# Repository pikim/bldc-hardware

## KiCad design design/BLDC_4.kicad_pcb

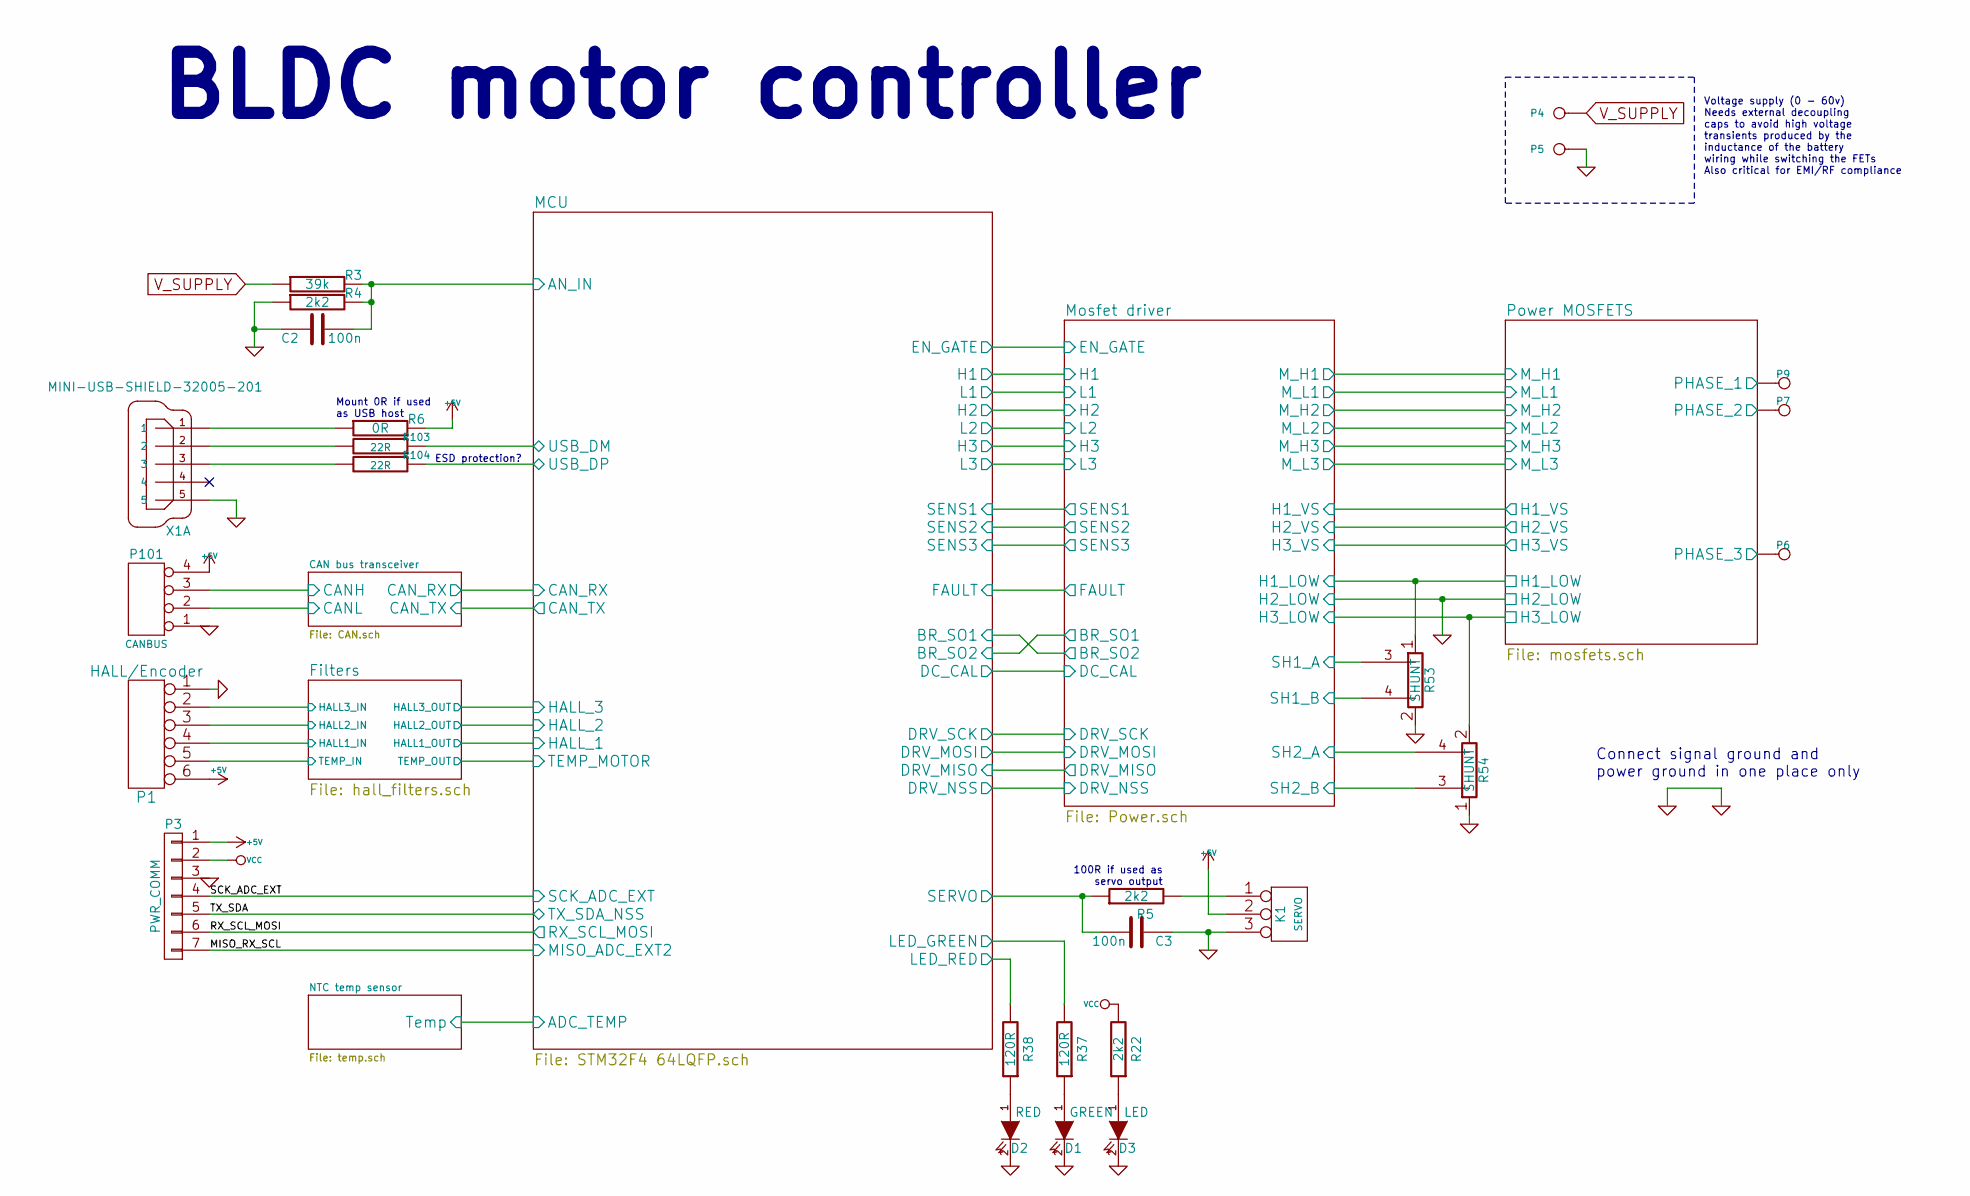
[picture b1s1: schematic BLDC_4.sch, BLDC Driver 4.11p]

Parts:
C2, C3: 100n; SMD-0603_c
D1: GREEN; LED-0603
D2: RED; LED-0603
D3: LED; LED-0603
K1: SERVO; pinhead-1X03
P1: HALL/Encoder; b6b-ph-kl
P3: PWR_COMM; b7b-ph-kl
P4: IN+; 1PAD_4x5mm
P5: IN-; 1PAD_4x5mm
P6: MOTOR1; 1PAD_4x5mm
P7: MOTOR2; 1PAD_4x5mm
P9: MOTOR3; 1PAD_4x5mm
P101: CANBUS; b4b-ph-kl
R3: 39k; SMD-0603_r
R4, R5, R22: 2k2; SMD-0603_r
R6: 0R; SMD-0603_r
R37, R38: 120R; SMD-0603_r
R53, R54: SHUNT; WSLP2726
R103, R104: 22R; SMD-0603_r
X1: MINI-USB-SHIELD-32005-201; USB-UX60R-MB-5ST

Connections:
+5V: K1.2 (PM), P1.6, P3.1, P101.4, R6.2; also elsewhere on the board
/CAN bus transceiver/CANH: P101.3; also elsewhere on the board
/CAN bus transceiver/CANL: P101.2; also elsewhere on the board
/Filters/HALL1_IN: P1.4; also elsewhere on the board
/Filters/HALL2_IN: P1.3; also elsewhere on the board
/Filters/HALL3_IN: P1.2; also elsewhere on the board
/Filters/TEMP_IN: P1.5; also elsewhere on the board
/MCU/AN_IN: C2.2, R3.2, R4.2; also elsewhere on the board
/MCU/LED_GREEN: R37.2; also elsewhere on the board
/MCU/LED_RED: R38.2; also elsewhere on the board
/MCU/MISO_ADC_EXT2: P3.7; also elsewhere on the board
/MCU/RX_SCL_MOSI: P3.6; also elsewhere on the board
/MCU/SCK_ADC_EXT: P3.4; also elsewhere on the board
/MCU/SERVO: C3.2, R5.1; also elsewhere on the board
/MCU/TX_SDA_NSS: P3.5; also elsewhere on the board
/MCU/USB_DM: R103.1; also elsewhere on the board
/MCU/USB_DP: R104.1; also elsewhere on the board
/Mosfet driver/H1_LOW: R53.1; also elsewhere on the board
/Mosfet driver/H1_VS: P9.1; also elsewhere on the board
/Mosfet driver/H2_VS: P7.1; also elsewhere on the board
/Mosfet driver/H3_LOW: R54.2; also elsewhere on the board
/Mosfet driver/H3_VS: P6.1; also elsewhere on the board
/Mosfet driver/SH1_A: R53.3; also elsewhere on the board
/Mosfet driver/SH1_B: R53.4; also elsewhere on the board
/Mosfet driver/SH2_A: R54.4; also elsewhere on the board
/Mosfet driver/SH2_B: R54.3; also elsewhere on the board
GND: C2.1, C3.1, D1.2 (K), D2.2 (K), D3.2 (K), K1.3, P1.1, P3.3, P5.1, P101.1, R4.1, R53.2, R54.1, X1.5; also elsewhere on the board
unnamed: D1.1 (A), R37.1
unnamed: D2.1 (A), R38.1
unnamed: D3.1 (A), R22.1
unnamed: K1.1, R5.2
unnamed: R6.1, X1.1
unnamed: R103.2, X1.2
unnamed: R104.2, X1.3
VCC: P3.2, R22.2; also elsewhere on the board
V_SUPPLY: P4.1, R3.1; also elsewhere on the board

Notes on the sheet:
100R if used as servo output
Mount 0R if used as USB host
ESD protection?
BLDC motor controller
Voltage supply (0 - 60v) Needs external decoupling caps to avoid high voltage transients produced by the inductance of the battery wiring while switching the FETs Also critical for EMI/RF compliance
Connect signal ground and power ground in one place only

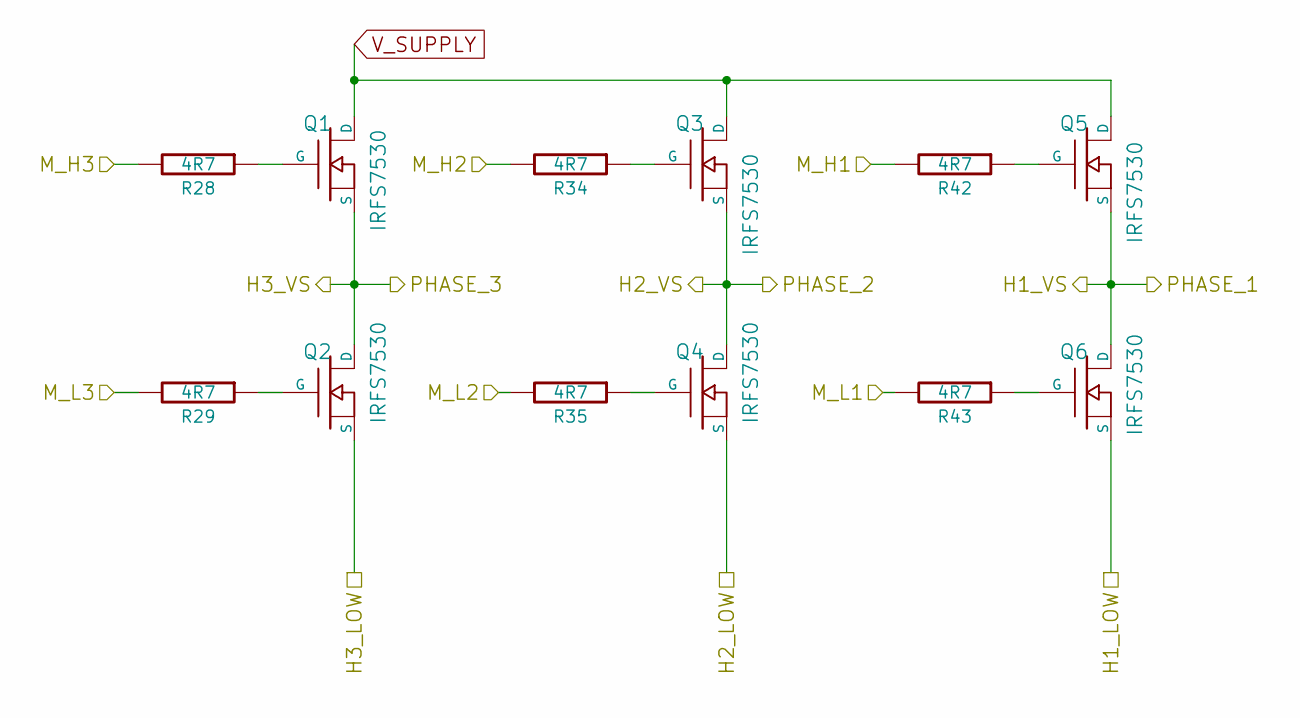
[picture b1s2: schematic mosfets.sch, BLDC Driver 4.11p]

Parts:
Q1, Q2, Q3, Q4, Q5, Q6: IRFS7530; D2PAK-7-GDS
R28, R29, R34, R35, R42, R43: 4R7; SMD-0603_r

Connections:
/Mosfet driver/H1_LOW: Q6.S; also elsewhere on the board
/Mosfet driver/H1_VS: Q5.S, Q6.D; also elsewhere on the board
/Mosfet driver/H2_VS: Q3.S, Q4.D; also elsewhere on the board
/Mosfet driver/H3_LOW: Q2.S; also elsewhere on the board
/Mosfet driver/H3_VS: Q1.S, Q2.D; also elsewhere on the board
/Mosfet driver/M_H1: R42.2; also elsewhere on the board
/Mosfet driver/M_H2: R34.2; also elsewhere on the board
/Mosfet driver/M_H3: R28.2; also elsewhere on the board
/Mosfet driver/M_L1: R43.2; also elsewhere on the board
/Mosfet driver/M_L2: R35.2; also elsewhere on the board
/Mosfet driver/M_L3: R29.2; also elsewhere on the board
GND: Q4.S; also elsewhere on the board
unnamed: Q1.G, R28.1
unnamed: Q2.G, R29.1
unnamed: Q3.G, R34.1
unnamed: Q4.G, R35.1
unnamed: Q5.G, R42.1
unnamed: Q6.G, R43.1
V_SUPPLY: Q1.D, Q3.D, Q5.D; also elsewhere on the board

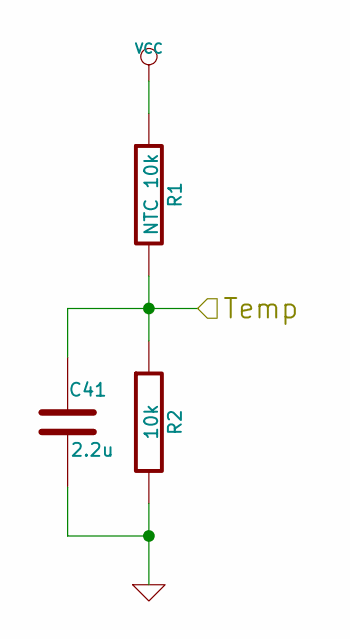
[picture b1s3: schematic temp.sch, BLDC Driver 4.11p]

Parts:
C41: 2.2u; SMD-0603_c; Part# GRM188R61C225KAAD or GRM188C81A225KAAD
R1: NTC 10k; SMD-0603_r
R2: 10k; SMD-0603_r

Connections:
/MCU/ADC_TEMP: C41.1, R1.2, R2.1; also elsewhere on the board
GND: C41.2, R2.2; also elsewhere on the board
VCC: R1.1; also elsewhere on the board

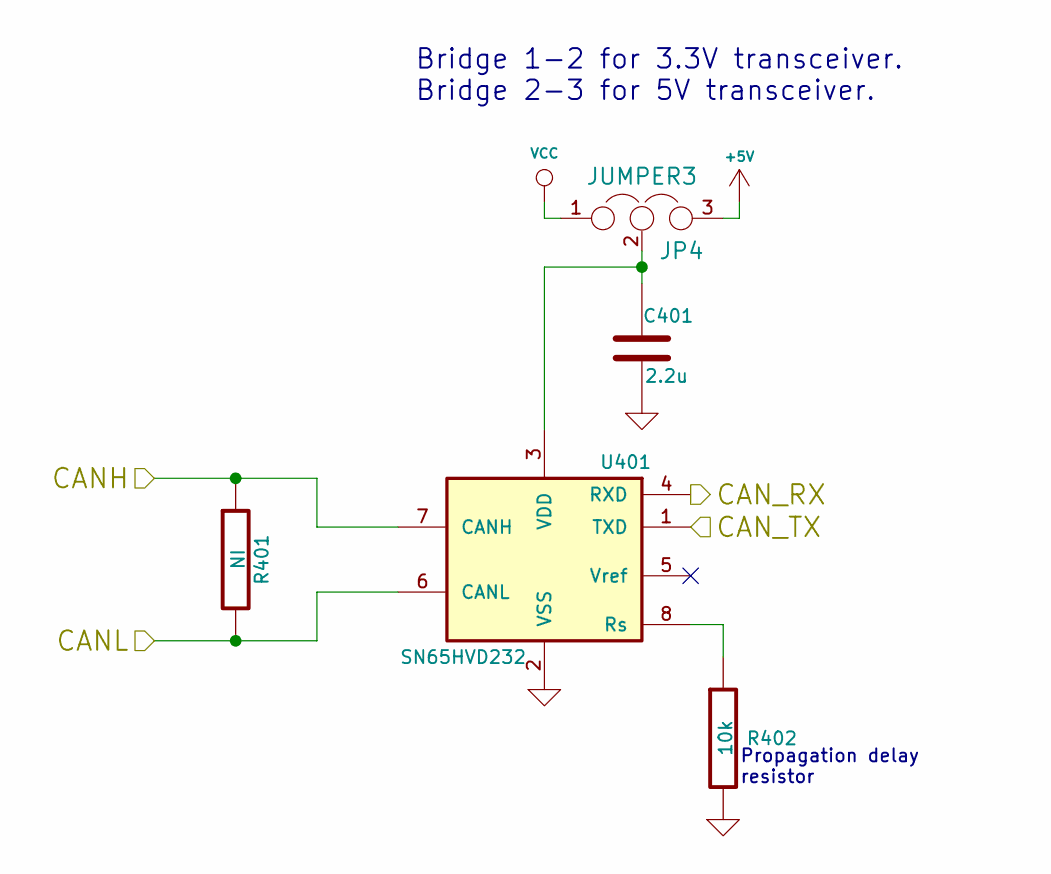
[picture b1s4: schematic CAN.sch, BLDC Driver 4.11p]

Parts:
C401: 2.2u; SMD-0603_c; Part# GRM188R61C225KAAD or GRM188C81A225KAAD
JP4: JUMPER3; S_JUMPER_3
R401: NI; SMD-0603_r
R402: 10k; SMD-0603_r
U401: SN65HVD232; SOIC-8-W

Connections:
+5V: JP4.3; also elsewhere on the board
/CAN bus transceiver/CANH: R401.1, U401.7 (CANH); also elsewhere on the board
/CAN bus transceiver/CANL: R401.2, U401.6 (CANL); also elsewhere on the board
/CAN bus transceiver/CAN_RX: U401.4 (RXD); also elsewhere on the board
/CAN bus transceiver/CAN_TX: U401.1 (TXD); also elsewhere on the board
GND: C401.2, R402.2, U401.2 (VSS); also elsewhere on the board
unnamed: C401.1, JP4.2, U401.3 (VDD)
unnamed: R402.1, U401.8 (Rs)
VCC: JP4.1; also elsewhere on the board

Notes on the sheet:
Propagation delay resistor
Bridge 1-2 for 3.3V transceiver. Bridge 2-3 for 5V transceiver.

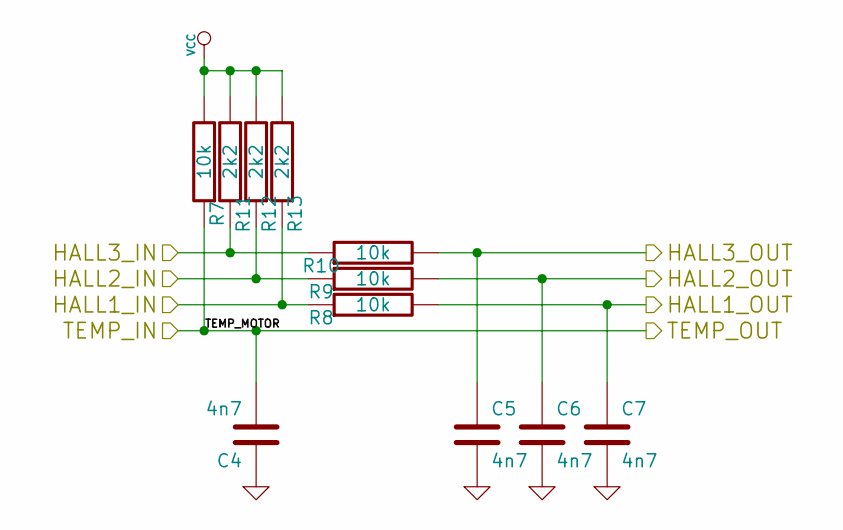
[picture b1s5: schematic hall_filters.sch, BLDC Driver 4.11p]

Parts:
C4, C5, C6, C7: 4n7; SMD-0603_c
R7, R8, R9, R10: 10k; SMD-0603_r
R11, R12, R13: 2k2; SMD-0603_r

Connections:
/Filters/HALL1_IN: R8.1, R13.1; also elsewhere on the board
/Filters/HALL1_OUT: C7.1, R8.2; also elsewhere on the board
/Filters/HALL2_IN: R9.1, R12.1; also elsewhere on the board
/Filters/HALL2_OUT: C6.1, R9.2; also elsewhere on the board
/Filters/HALL3_IN: R10.1, R11.1; also elsewhere on the board
/Filters/HALL3_OUT: C5.1, R10.2; also elsewhere on the board
/Filters/TEMP_IN: C4.2, R7.1; also elsewhere on the board
GND: C4.1, C5.2, C6.2, C7.2; also elsewhere on the board
VCC: R7.2, R11.2, R12.2, R13.2; also elsewhere on the board

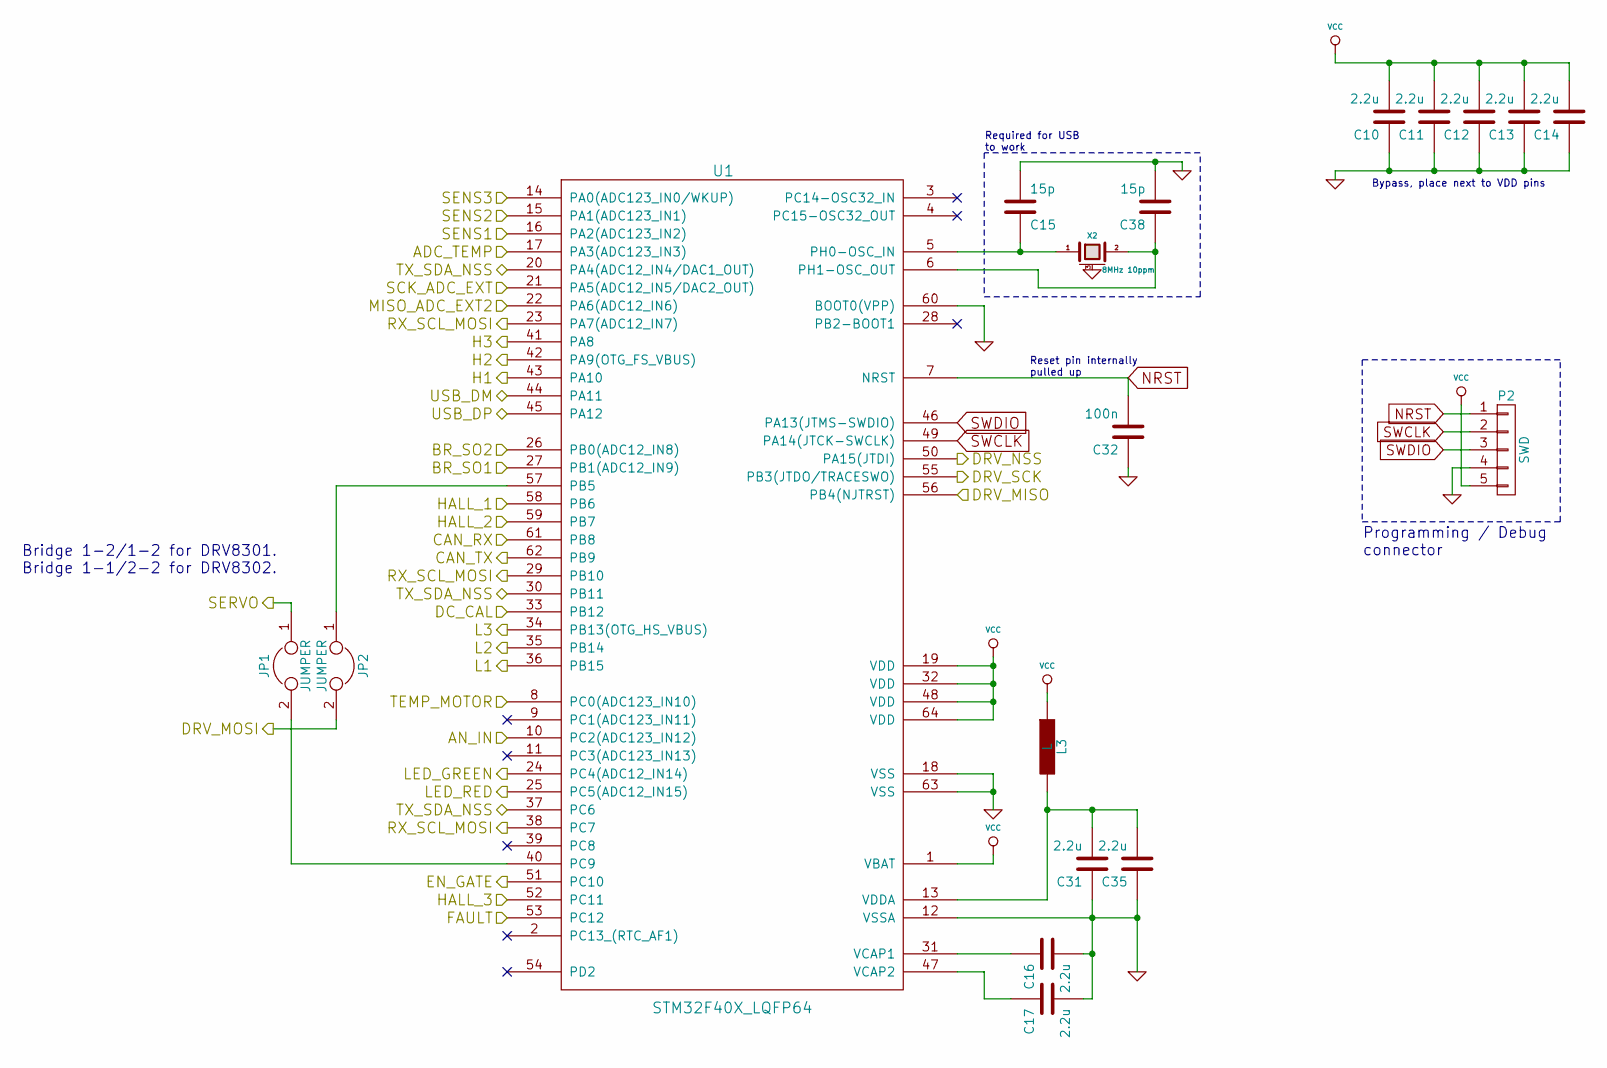
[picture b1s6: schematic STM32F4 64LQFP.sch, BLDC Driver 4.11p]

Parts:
C10, C11, C12, C13, C14, C16, C17, C31, C35: 2.2u; SMD-0603_c; Part# GRM188R61C225KAAD or GRM188C81A225KAAD
C15, C38: 15p; SMD-0603_c
C32: 100n; SMD-0603_c
JP1, JP2: JUMPER; S_JUMPER_2
L3: L; SMD-0603_r
P2: SWD; Pin_Header_Straight_1x05
U1: STM32F40X_LQFP64; lqfp64_pad_mod
X2: 8MHz 10ppm; Crystal_5x3mm; Part# ABM3B-8.0-10-1UT

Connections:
/CAN bus transceiver/CAN_RX: U1.61 (PB8); also elsewhere on the board
/CAN bus transceiver/CAN_TX: U1.62 (PB9); also elsewhere on the board
/Filters/HALL1_OUT: U1.58 (PB6); also elsewhere on the board
/Filters/HALL2_OUT: U1.59 (PB7); also elsewhere on the board
/Filters/HALL3_OUT: U1.52 (PC11); also elsewhere on the board
/Filters/TEMP_IN: U1.8 (PC0(ADC123_IN10)); also elsewhere on the board
/MCU/ADC_TEMP: U1.17 (PA3(ADC123_IN3)); also elsewhere on the board
/MCU/AN_IN: U1.10 (PC2(ADC123_IN12)); also elsewhere on the board
/MCU/BR_SO1: U1.27 (PB1(ADC12_IN9)); also elsewhere on the board
/MCU/DC_CAL: U1.33 (PB12); also elsewhere on the board
/MCU/DRV_MISO: U1.56 (PB4(NJTRST)); also elsewhere on the board
/MCU/DRV_MOSI: JP2.2; also elsewhere on the board
/MCU/DRV_NSS: U1.50 (PA15(JTDI)); also elsewhere on the board
/MCU/DRV_SCK: U1.55 (PB3(JTDO/TRACESWO)); also elsewhere on the board
/MCU/EN_GATE: U1.51 (PC10); also elsewhere on the board
/MCU/FAULT: U1.53 (PC12); also elsewhere on the board
/MCU/H1: U1.43 (PA10); also elsewhere on the board
/MCU/H2: U1.42 (PA9(OTG_FS_VBUS)); also elsewhere on the board
/MCU/H3: U1.41 (PA8); also elsewhere on the board
/MCU/L1: U1.36 (PB15); also elsewhere on the board
/MCU/L2: U1.35 (PB14); also elsewhere on the board
/MCU/L3: U1.34 (PB13(OTG_HS_VBUS)); also elsewhere on the board
/MCU/LED_GREEN: U1.24 (PC4(ADC12_IN14)); also elsewhere on the board
/MCU/LED_RED: U1.25 (PC5(ADC12_IN15)); also elsewhere on the board
/MCU/MISO_ADC_EXT2: U1.22 (PA6(ADC12_IN6)); also elsewhere on the board
/MCU/RX_SCL_MOSI: U1.23 (PA7(ADC12_IN7)), U1.29 (PB10), U1.38 (PC7); also elsewhere on the board
/MCU/SCK_ADC_EXT: U1.21 (PA5(ADC12_IN5/DAC2_OUT)); also elsewhere on the board
/MCU/SENS1: U1.16 (PA2(ADC123_IN2)); also elsewhere on the board
/MCU/SENS2: U1.15 (PA1(ADC123_IN1)); also elsewhere on the board
/MCU/SENS3: U1.14 (PA0(ADC123_IN0/WKUP)); also elsewhere on the board
/MCU/SERVO: JP1.1; also elsewhere on the board
/MCU/TX_SDA_NSS: U1.20 (PA4(ADC12_IN4/DAC1_OUT)), U1.30 (PB11), U1.37 (PC6); also elsewhere on the board
/MCU/USB_DM: U1.44 (PA11); also elsewhere on the board
/MCU/USB_DP: U1.45 (PA12); also elsewhere on the board
/Mosfet driver/BR_SO1: U1.26 (PB0(ADC12_IN8)); also elsewhere on the board
GND: C10.1, C11.1, C12.1, C13.1, C14.1, C15.2, C16.2, C17.2, C31.1, C32.1, C35.1, C38.2, P2.4, U1.12 (VSSA), U1.18 (VSS), U1.60 (BOOT0(VPP)), U1.63 (VSS), X2.3 (case); also elsewhere on the board
NRST: C32.2, P2.1, U1.7 (NRST)
unnamed: C15.1, U1.5 (PH0-OSC_IN), X2.1
unnamed: C16.1, U1.31 (VCAP1)
unnamed: C17.1, U1.47 (VCAP2)
unnamed: C31.2, C35.2, L3.2, U1.13 (VDDA)
unnamed: C38.1, U1.6 (PH1-OSC_OUT), X2.2
unnamed: JP1.2, U1.40 (PC9)
unnamed: JP2.1, U1.57 (PB5)
SWCLK: P2.2, U1.49 (PA14(JTCK-SWCLK))
SWDIO: P2.3, U1.46 (PA13(JTMS-SWDIO))
VCC: C10.2, C11.2, C12.2, C13.2, C14.2, L3.1, P2.5, U1.1 (VBAT), U1.19 (VDD), U1.32 (VDD), U1.48 (VDD), U1.64 (VDD); also elsewhere on the board

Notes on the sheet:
Programming / Debug connector
Reset pin internally pulled up
Required for USB to work
Bypass, place next to VDD pins
Bridge 1-2/1-2 for DRV8301. Bridge 1-1/2-2 for DRV8302.

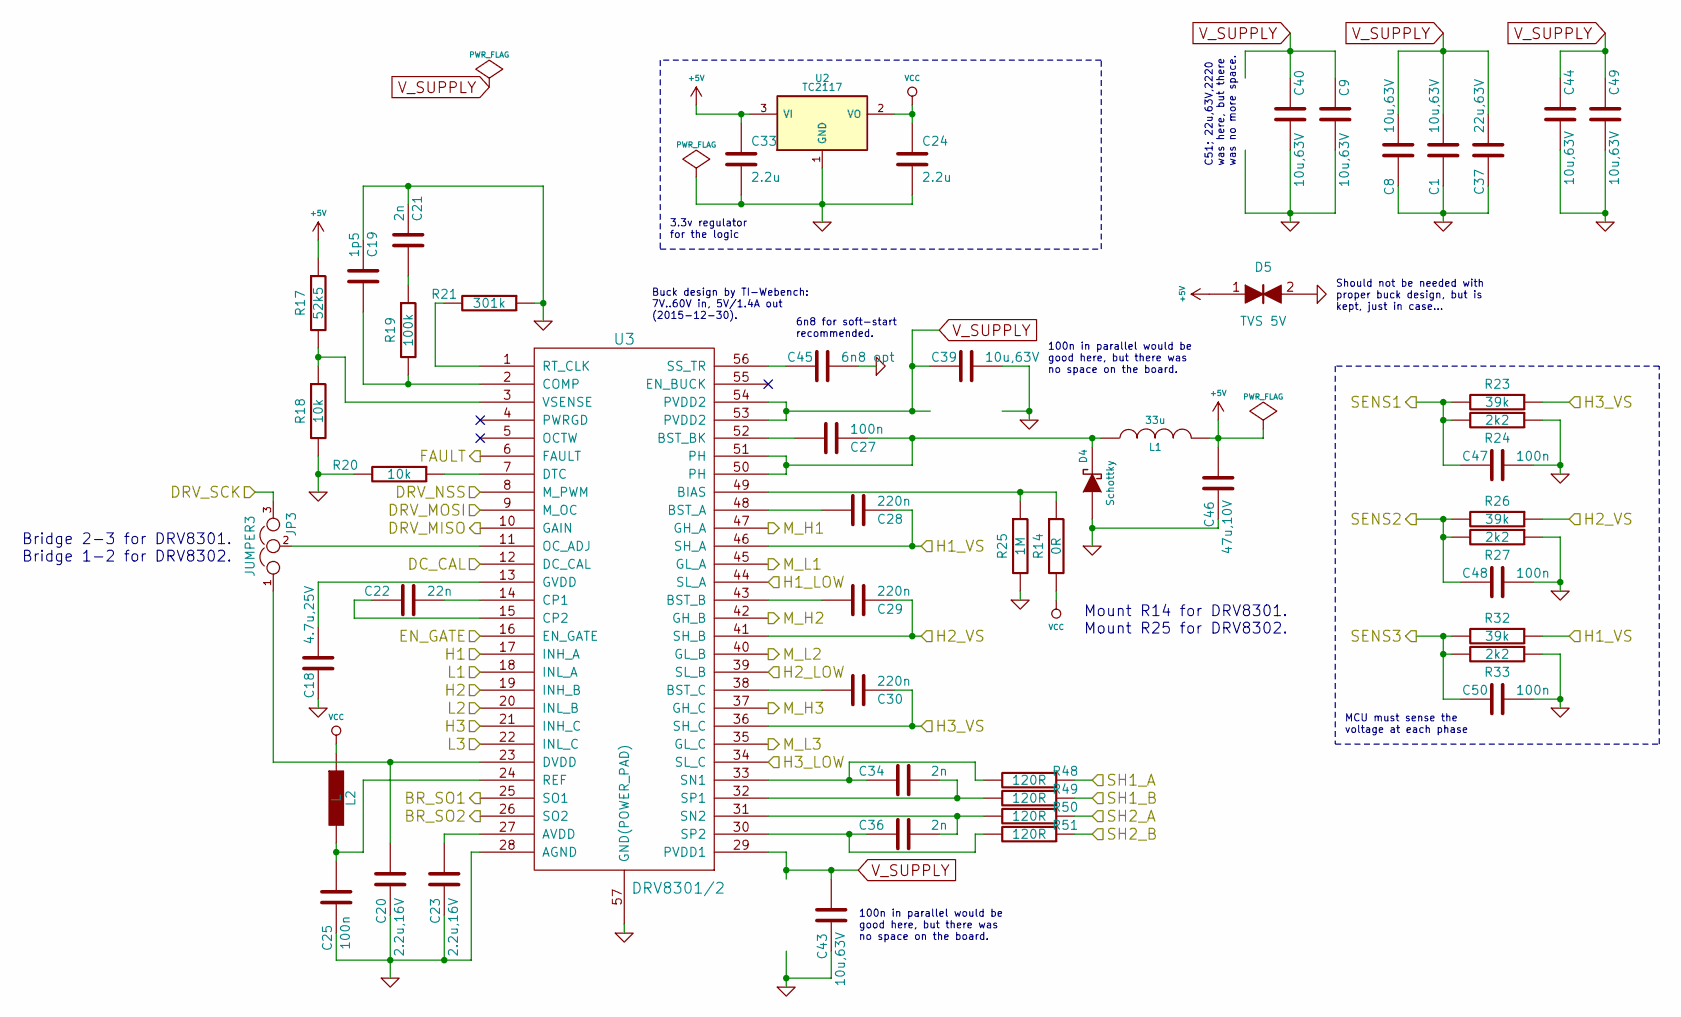
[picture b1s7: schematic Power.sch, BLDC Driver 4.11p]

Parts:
C1, C8, C9, C39, C40, C43, C44, C49: 10u,63V; c_1210; Part# GRM32ER71J106KA12
C18: 4.7u,25V; SMD-0603_c; Part# GRM188R61E475KE15
C19: 1p5; SMD-0603_c
C20, C23: 2.2u,16V; SMD-0603_c; Part# GRM188R61C225KAAD
C21, C34, C36: 2n; SMD-0603_c
C22: 22n; SMD-0603_c
C24, C33: 2.2u; SMD-0603_c; Part# GRM188R61C225KAAD or GRM188C81A225KAAD
C25, C27, C47, C48, C50: 100n; SMD-0603_c
C28, C29, C30: 220n; SMD-0603_c
C37: 22u,63V; c_2220; Part# KRM55WR71J226MH01
C45: 6n8 opt; SMD-0603_c
C46: 47u,10V; c_1210; Part# GRM32ER61A476KE20
D4: Schottky; SMA_Standard
D5: TVS 5V; SMA_Standard
JP3: JUMPER3; S_JUMPER_3
L1: 33u; inductor_smd_6x6mm
L2: L; SMD-0603_r
R14: 0R; SMD-0603_r
R17: 52k5; SMD-0603_r
R18, R20: 10k; SMD-0603_r
R19: 100k; SMD-0603_r
R21: 301k; SMD-0603_r
R23, R26, R32: 39k; SMD-0603_r
R24, R27, R33: 2k2; SMD-0603_r
R25: 1M; SMD-0603_r
R48, R49, R50, R51: 120R; SMD-0603_r
U2: TC2117; SOT-223
U3: DRV8301/2; TSSOP-56-PP

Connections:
+5V: C33.1, C46.1, D5.1, L1.2, R17.1, U2.3 (VI); also elsewhere on the board
/MCU/BR_SO1: U3.26 (SO2); also elsewhere on the board
/MCU/DC_CAL: U3.12 (DC_CAL); also elsewhere on the board
/MCU/DRV_MISO: U3.10 (GAIN); also elsewhere on the board
/MCU/DRV_MOSI: U3.9 (M_OC); also elsewhere on the board
/MCU/DRV_NSS: U3.8 (M_PWM); also elsewhere on the board
/MCU/DRV_SCK: JP3.3; also elsewhere on the board
/MCU/EN_GATE: U3.16 (EN_GATE); also elsewhere on the board
/MCU/FAULT: U3.6 (FAULT); also elsewhere on the board
/MCU/H1: U3.17 (INH_A); also elsewhere on the board
/MCU/H2: U3.19 (INH_B); also elsewhere on the board
/MCU/H3: U3.21 (INH_C); also elsewhere on the board
/MCU/L1: U3.18 (INL_A); also elsewhere on the board
/MCU/L2: U3.20 (INL_B); also elsewhere on the board
/MCU/L3: U3.22 (INL_C); also elsewhere on the board
/MCU/SENS1: C47.2, R23.2, R24.2; also elsewhere on the board
/MCU/SENS2: C48.2, R26.2, R27.2; also elsewhere on the board
/MCU/SENS3: C50.2, R32.2, R33.2; also elsewhere on the board
/Mosfet driver/BR_SO1: U3.25 (SO1); also elsewhere on the board
/Mosfet driver/H1_LOW: U3.44 (SL_A); also elsewhere on the board
/Mosfet driver/H1_VS: C28.1, R32.1, U3.46 (SH_A); also elsewhere on the board
/Mosfet driver/H2_VS: C29.1, R26.1, U3.41 (SH_B); also elsewhere on the board
/Mosfet driver/H3_LOW: U3.34 (SL_C); also elsewhere on the board
/Mosfet driver/H3_VS: C30.1, R23.1, U3.36 (SH_C); also elsewhere on the board
/Mosfet driver/M_H1: U3.47 (GH_A); also elsewhere on the board
/Mosfet driver/M_H2: U3.42 (GH_B); also elsewhere on the board
/Mosfet driver/M_H3: U3.37 (GH_C); also elsewhere on the board
/Mosfet driver/M_L1: U3.45 (GL_A); also elsewhere on the board
/Mosfet driver/M_L2: U3.40 (GL_B); also elsewhere on the board
/Mosfet driver/M_L3: U3.35 (GL_C); also elsewhere on the board
/Mosfet driver/SH1_A: R48.1; also elsewhere on the board
/Mosfet driver/SH1_B: R49.1; also elsewhere on the board
/Mosfet driver/SH2_A: R50.1; also elsewhere on the board
/Mosfet driver/SH2_B: R51.1; also elsewhere on the board
GND: C1.1, C8.1, C9.1, C18.2, C19.1, C20.1, C21.1, C23.1, C24.2, C25.1, C33.2, C37.1, C39.1, C40.1, C43.2, C44.2, C45.1, C46.2, C47.1, C48.1, C49.2, C50.1, D4.1 (A), D5.2, R18.2, R20.2, R21.1, R24.1, R25.2, R27.1, R33.1, U2.1 (GND), U3.28 (AGND), U3.39 (SL_B), U3.57 (GND(POWER_PAD)); also elsewhere on the board
unnamed: C18.1, U3.13 (GVDD)
unnamed: C19.2, R19.2, U3.2 (COMP)
unnamed: C20.2, JP3.1, U3.23 (DVDD)
unnamed: C21.2, R19.1
unnamed: C22.1, U3.14 (CP1)
unnamed: C22.2, U3.15 (CP2)
unnamed: C23.2, U3.27 (AVDD)
unnamed: C25.2, L2.2, U3.24 (REF)
unnamed: C27.1, D4.2 (K), L1.1, U3.50 (PH), U3.51 (PH)
unnamed: C27.2, U3.52 (BST_BK)
unnamed: C28.2, U3.48 (BST_A)
unnamed: C29.2, U3.43 (BST_B)
unnamed: C30.2, U3.38 (BST_C)
unnamed: C34.1, R48.2, U3.33 (SN1)
unnamed: C34.2, R49.2, U3.32 (SP1)
unnamed: C36.1, R51.2, U3.30 (SP2)
unnamed: C36.2, R50.2, U3.31 (SN2)
unnamed: C45.2, U3.56 (SS_TR)
unnamed: JP3.2, U3.11 (OC_ADJ)
unnamed: R14.1, R25.1, U3.49 (BIAS)
unnamed: R17.2, R18.1, U3.3 (VSENSE)
unnamed: R20.1, U3.7 (DTC)
unnamed: R21.2, U3.1 (RT_CLK)
VCC: C24.1, L2.1, R14.2, U2.2 (VO); also elsewhere on the board
V_SUPPLY: C1.2, C8.2, C9.2, C37.2, C39.2, C40.2, C43.1, C44.1, C49.1, U3.29 (PVDD1), U3.53 (PVDD2), U3.54 (PVDD2); also elsewhere on the board

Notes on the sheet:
MCU must sense the voltage at each phase
3.3v regulator for the logic
Buck design by TI-Webench: 7V..60V in, 5V/1.4A out (2015-12-30).
C51; 22u,63V,2220 was here, but there was no more space.
100n in parallel would be good here, but there was no space on the board.
6n8 for soft-start recommended.
Should not be needed with proper buck design, but is kept, just in case...
Bridge 2-3 for DRV8301. Bridge 1-2 for DRV8302.
Mount R14 for DRV8301. Mount R25 for DRV8302.

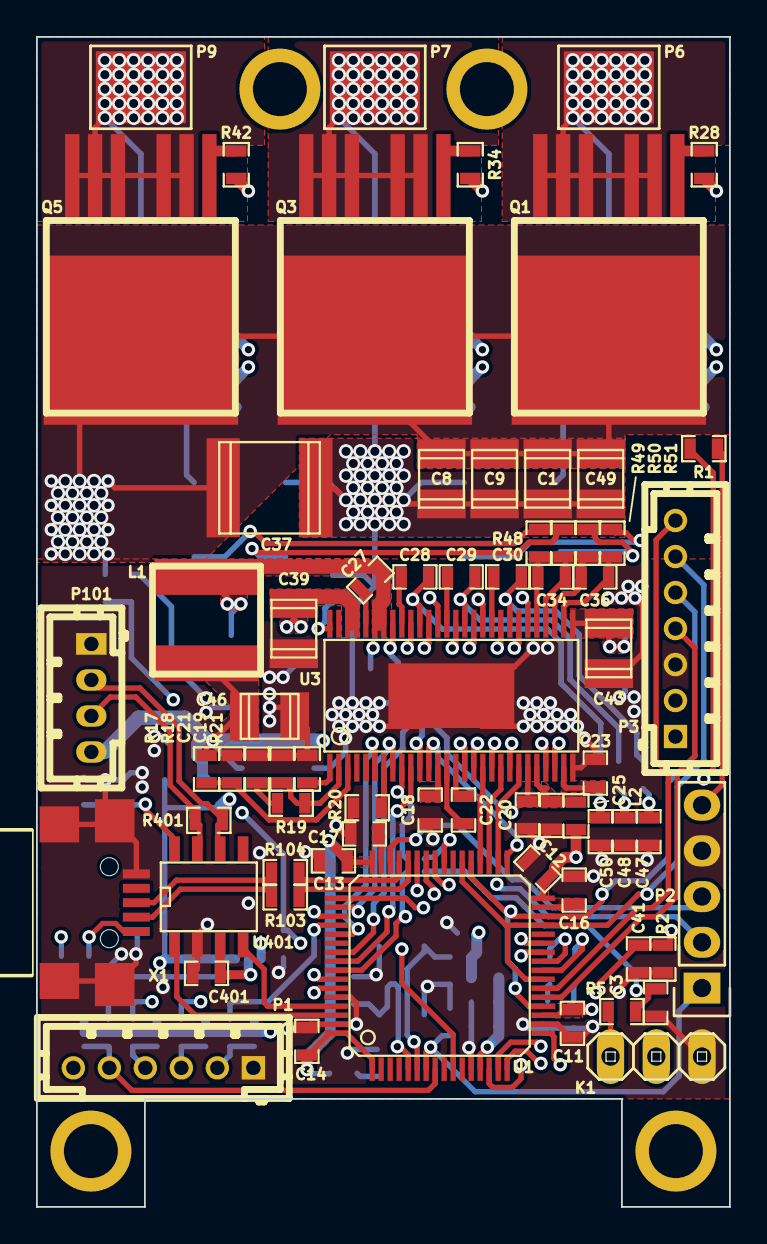
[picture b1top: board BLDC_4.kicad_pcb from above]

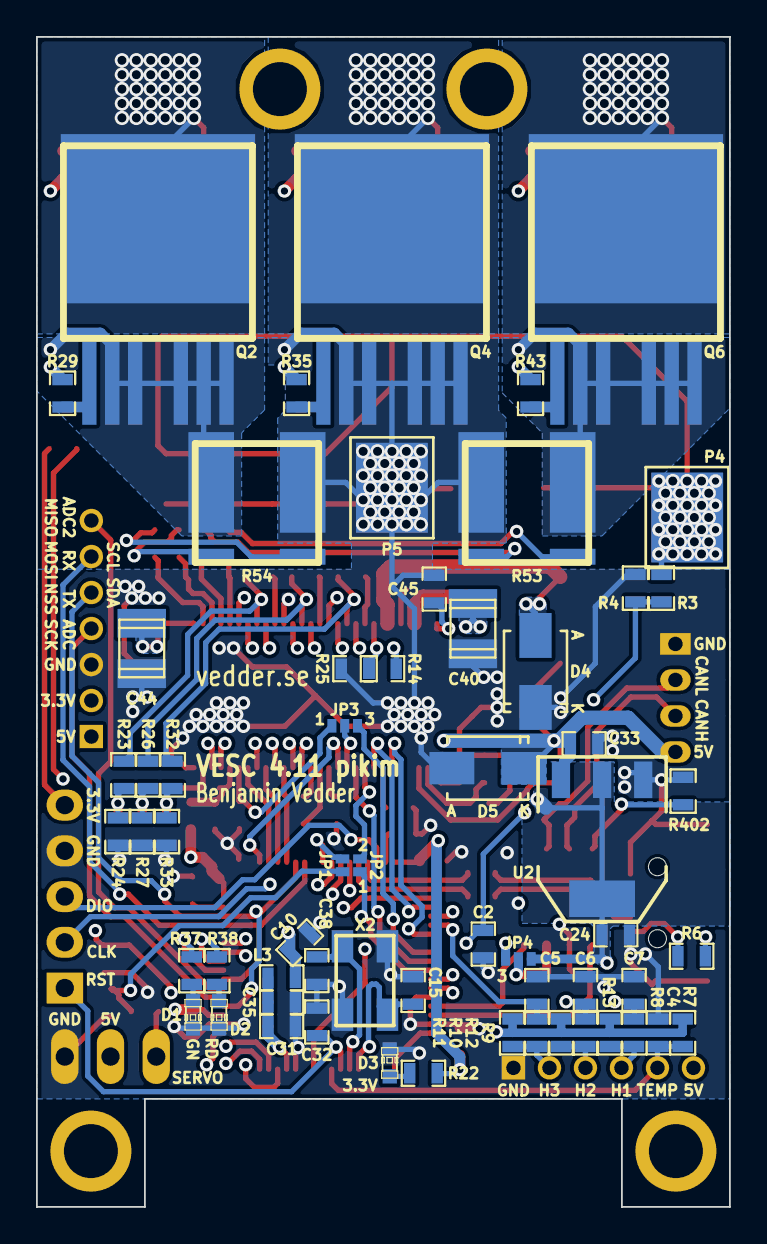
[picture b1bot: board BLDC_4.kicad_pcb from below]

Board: 4 copper layers, 38.5 x 65.0 mm, 128 parts (60 on the bottom side), 107 nets.

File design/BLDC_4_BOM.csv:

Reference,Value,Footprint,Count,Part#
C3,100n,CRF1:SMD-0603_c,1,
R5,2k2,CRF1:SMD-0603_r,1,
C2,100n,CRF1:SMD-0603_c,1,
K1,SERVO,CRF1:pinhead-1X03,1,
R4,2k2,CRF1:SMD-0603_r,1,
R3,39k,CRF1:SMD-0603_r,1,
X1,MINI-USB-SHIELD-32005-201,CRF1:USB-UX60R-MB-5ST,1,
R6,0R,CRF1:SMD-0603_r,1,
P5,IN-,CRF1:1PAD_4x5mm,1,
P4,IN+,CRF1:1PAD_4x5mm,1,
P9,MOTOR3,CRF1:1PAD_4x5mm,1,
P7,MOTOR2,CRF1:1PAD_4x5mm,1,
P6,MOTOR1,CRF1:1PAD_4x5mm,1,
R103,22R,CRF1:SMD-0603_r,1,
R104,22R,CRF1:SMD-0603_r,1,
R38,120R,CRF1:SMD-0603_r,1,
D2,RED,LEDs:LED-0603,1,
R37,120R,CRF1:SMD-0603_r,1,
D1,GREEN,LEDs:LED-0603,1,
D3,LED,LEDs:LED-0603,1,
R22,2k2,CRF1:SMD-0603_r,1,
P101,CANBUS,JST conn:b4b-ph-kl,1,
R53,SHUNT,CRF1:WSLP2726,1,
R54,SHUNT,CRF1:WSLP2726,1,
P3,PWR_COMM,pikim:b7b-ph-kl,1,
P1,HALL/Encoder,pikim:b6b-ph-kl,1,
Q1,IRFS7530,pikim:D2PAK-7-GDS,1,
Q2,IRFS7530,pikim:D2PAK-7-GDS,1,
R29,4R7,CRF1:SMD-0603_r,1,
R28,4R7,CRF1:SMD-0603_r,1,
R34,4R7,CRF1:SMD-0603_r,1,
R35,4R7,CRF1:SMD-0603_r,1,
Q4,IRFS7530,pikim:D2PAK-7-GDS,1,
Q3,IRFS7530,pikim:D2PAK-7-GDS,1,
Q5,IRFS7530,pikim:D2PAK-7-GDS,1,
Q6,IRFS7530,pikim:D2PAK-7-GDS,1,
R43,4R7,CRF1:SMD-0603_r,1,
R42,4R7,CRF1:SMD-0603_r,1,
R1,NTC 10k,CRF1:SMD-0603_r,1,
R2,10k,CRF1:SMD-0603_r,1,
C41,2.2u,CRF1:SMD-0603_c,1,GRM188R61C225KAAD or GRM188C81A225KAAD
U401,SN65HVD232,CRF1:SOIC-8-W,1,
C401,2.2u,CRF1:SMD-0603_c,1,GRM188R61C225KAAD or GRM188C81A225KAAD
R401,NI,CRF1:SMD-0603_r,1,
R402,10k,CRF1:SMD-0603_r,1,
JP4,JUMPER3,open-project:S_JUMPER_3,1,
R7,10k,CRF1:SMD-0603_r,1,
R8,10k,CRF1:SMD-0603_r,1,
R9,10k,CRF1:SMD-0603_r,1,
R10,10k,CRF1:SMD-0603_r,1,
C5,4n7,CRF1:SMD-0603_c,1,
C6,4n7,CRF1:SMD-0603_c,1,
C7,4n7,CRF1:SMD-0603_c,1,
R11,2k2,CRF1:SMD-0603_r,1,
R12,2k2,CRF1:SMD-0603_r,1,
R13,2k2,CRF1:SMD-0603_r,1,
C4,4n7,CRF1:SMD-0603_c,1,
U1,STM32F40X_LQFP64,CRF1:lqfp64_pad_mod,1,
C17,2.2u,CRF1:SMD-0603_c,1,GRM188R61C225KAAD or GRM188C81A225KAAD
C16,2.2u,CRF1:SMD-0603_c,1,GRM188R61C225KAAD or GRM188C81A225KAAD
C15,15p,CRF1:SMD-0603_c,1,
C38,15p,CRF1:SMD-0603_c,1,
C31,2.2u,CRF1:SMD-0603_c,1,GRM188R61C225KAAD or GRM188C81A225KAAD
C35,2.2u,CRF1:SMD-0603_c,1,GRM188R61C225KAAD or GRM188C81A225KAAD
C32,100n,CRF1:SMD-0603_c,1,
C10,2.2u,CRF1:SMD-0603_c,1,GRM188R61C225KAAD or GRM188C81A225KAAD
C11,2.2u,CRF1:SMD-0603_c,1,GRM188R61C225KAAD or GRM188C81A225KAAD
C14,2.2u,CRF1:SMD-0603_c,1,GRM188R61C225KAAD or GRM188C81A225KAAD
C12,2.2u,CRF1:SMD-0603_c,1,GRM188R61C225KAAD or GRM188C81A225KAAD
C13,2.2u,CRF1:SMD-0603_c,1,GRM188R61C225KAAD or GRM188C81A225KAAD
X2,8MHz 10ppm,CRF1:Crystal_5x3mm,1,ABM3B-8.0-10-1UT
JP2,JUMPER,open-project:S_JUMPER_2,1,
JP1,JUMPER,open-project:S_JUMPER_2,1,
P2,SWD,Pin_Headers:Pin_Header_Straight_1x05,1,
L3,L,CRF1:SMD-0603_r,1,
C28,220n,CRF1:SMD-0603_c,1,
D4,Schottky,Diodes_SMD:SMA_Standard,1,
R23,39k,CRF1:SMD-0603_r,1,
R24,2k2,CRF1:SMD-0603_r,1,
R27,2k2,CRF1:SMD-0603_r,1,
R26,39k,CRF1:SMD-0603_r,1,
R32,39k,CRF1:SMD-0603_r,1,
R33,2k2,CRF1:SMD-0603_r,1,
C29,220n,CRF1:SMD-0603_c,1,
C30,220n,CRF1:SMD-0603_c,1,
C27,100n,CRF1:SMD-0603_c,1,
L1,33u,pikim:inductor_smd_6x6mm,1,
C22,22n,CRF1:SMD-0603_c,1,
C18,"4.7u,25V",CRF1:SMD-0603_c,1,GRM188R61E475KE15
C20,"2.2u,16V",CRF1:SMD-0603_c,1,GRM188R61C225KAAD
C23,"2.2u,16V",CRF1:SMD-0603_c,1,GRM188R61C225KAAD
R20,10k,CRF1:SMD-0603_r,1,
R21,301k,CRF1:SMD-0603_r,1,
R17,52k5,CRF1:SMD-0603_r,1,
R18,10k,CRF1:SMD-0603_r,1,
R19,100k,CRF1:SMD-0603_r,1,
C21,2n,CRF1:SMD-0603_c,1,
C19,1p5,CRF1:SMD-0603_c,1,
C24,2.2u,CRF1:SMD-0603_c,1,GRM188R61C225KAAD or GRM188C81A225KAAD
R48,120R,CRF1:SMD-0603_r,1,
R49,120R,CRF1:SMD-0603_r,1,
R50,120R,CRF1:SMD-0603_r,1,
R51,120R,CRF1:SMD-0603_r,1,
C34,2n,CRF1:SMD-0603_c,1,
C36,2n,CRF1:SMD-0603_c,1,
C39,"10u,63V",w_smd_cap:c_1210,1,GRM32ER71J106KA12
C43,"10u,63V",w_smd_cap:c_1210,1,GRM32ER71J106KA12
C44,"10u,63V",w_smd_cap:c_1210,1,GRM32ER71J106KA12
C49,"10u,63V",w_smd_cap:c_1210,1,GRM32ER71J106KA12
C1,"10u,63V",w_smd_cap:c_1210,1,GRM32ER71J106KA12
C37,"22u,63V",w_smd_cap:c_2220,1,KRM55WR71J226MH01
U2,TC2117,CRF1:SOT-223,1,
C40,"10u,63V",w_smd_cap:c_1210,1,GRM32ER71J106KA12
C9,"10u,63V",w_smd_cap:c_1210,1,GRM32ER71J106KA12
C8,"10u,63V",w_smd_cap:c_1210,1,GRM32ER71J106KA12
JP3,JUMPER3,open-project:S_JUMPER_3,1,
R25,1M,CRF1:SMD-0603_r,1,
R14,0R,CRF1:SMD-0603_r,1,
U3,DRV8301/2,pikim:TSSOP-56-PP,1,
C25,100n,CRF1:SMD-0603_c,1,
L2,L,CRF1:SMD-0603_r,1,
C46,"47u,10V",w_smd_cap:c_1210,1,GRM32ER61A476KE20
C33,2.2u,CRF1:SMD-0603_c,1,GRM188R61C225KAAD or GRM188C81A225KAAD
C50,100n,CRF1:SMD-0603_c,1,
C48,100n,CRF1:SMD-0603_c,1,
C47,100n,CRF1:SMD-0603_c,1,
C45,6n8 opt,CRF1:SMD-0603_c,1,
D5,TVS 5V,Diodes_SMD:SMA_Standard,1,

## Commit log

2016-01-08 Implemented some improvements in schematic, but layout is completely new.
    Changes in schematic:
    - 3.3V or 5V CAN transceiver can be used
    - DRV8301 can also be used and configured via SPI
    - JTAG connector changed
    - Fixed pinning of P1
    - Some additional decoupling and/or filtering of analog signals
2016-01-10 Fixed some errors in v4.11p layout and gerber data. Increased revision to B.
2016-01-10 Fixed another error in v4.11p layout and gerber data. Increased revision to C.
